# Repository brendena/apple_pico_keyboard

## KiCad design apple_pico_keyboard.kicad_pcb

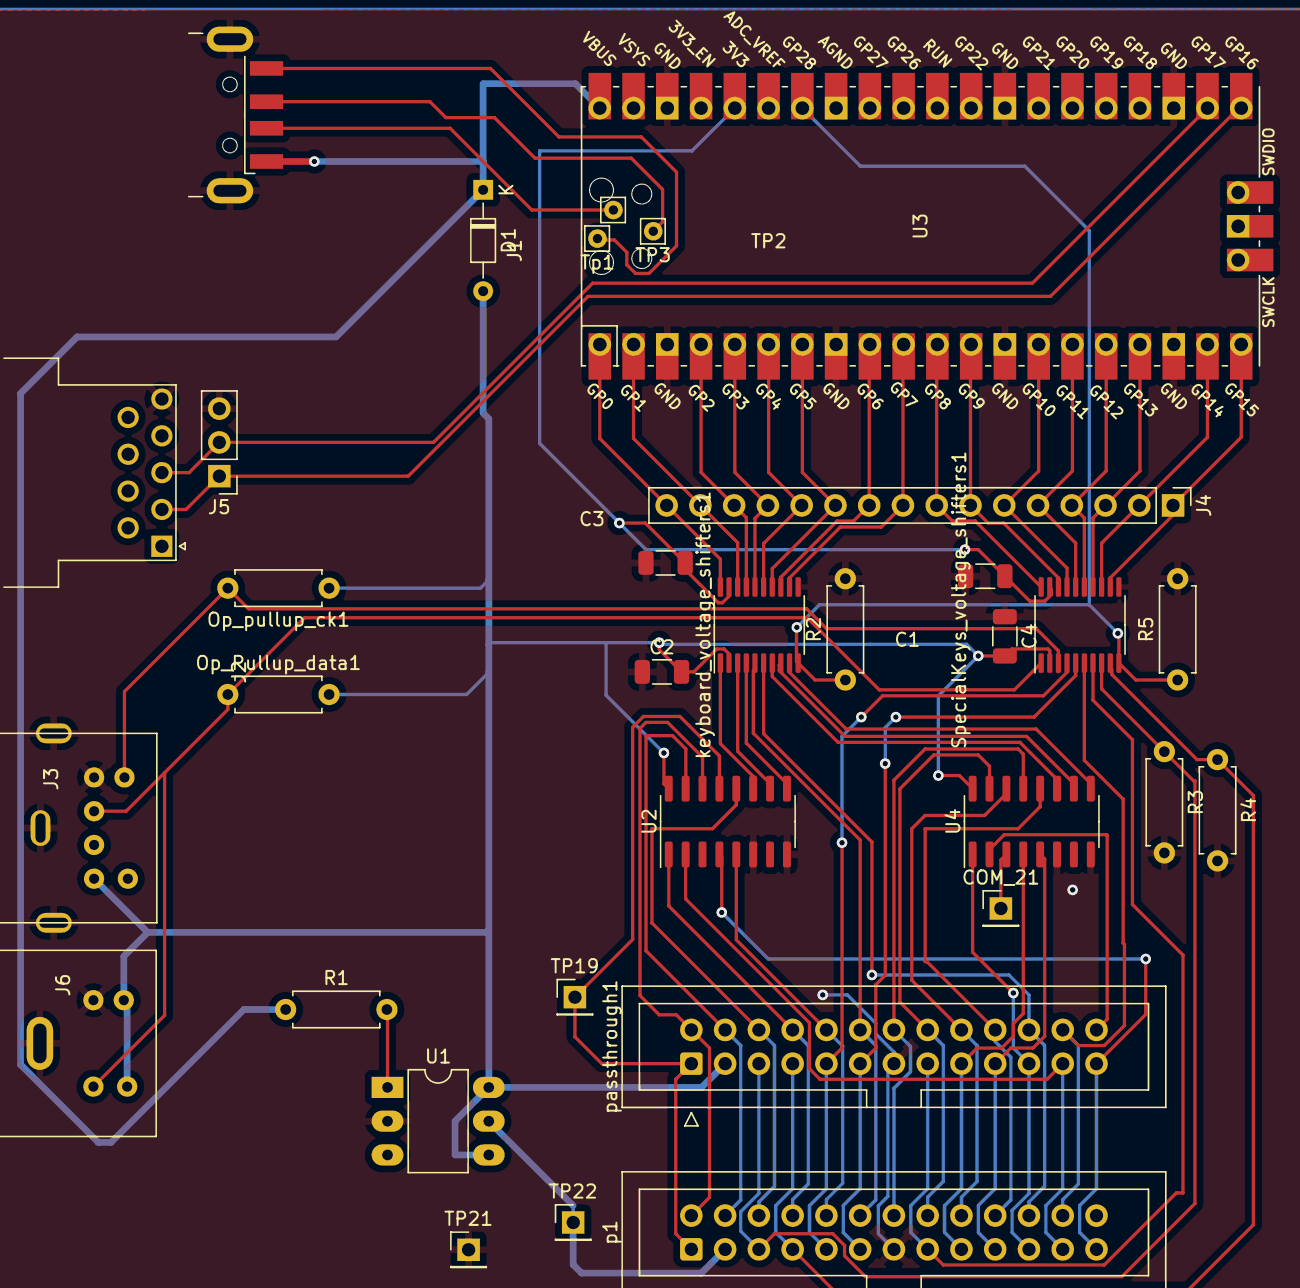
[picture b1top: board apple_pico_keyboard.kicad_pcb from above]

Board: 2 copper layers, 33 parts (0 on the bottom side), 61 nets.

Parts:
C1, C2, C3, C4: 0.1uf; C_1206_3216Metric
COM_21: TestPoint; PinHeader_1x01_P2.54mm_Vertical
D1: DIODE; D_DO-34_SOD68_P7.62mm_Horizontal
J1: USB_A; USB_A_CNCTech_1001-011-01101_Horizontal
J2: DB9_Female; DSUB-9_Female_Horizontal_P2.77x2.54mm_EdgePinOffset9.40mm
J3: Mini-DIN-6; MiniDin6
J4: Conn_01x16_Male; PinHeader_1x16_P2.54mm_Vertical
J5: Conn_01x03_Male; PinHeader_1x03_P2.54mm_Vertical
J6: Mini-DIN-4; MiniDin4
Op_Pullup_data1: 10k; R_Axial_DIN0207_L6.3mm_D2.5mm_P7.62mm_Horizontal
Op_pullup_ck1: 10k; R_Axial_DIN0207_L6.3mm_D2.5mm_P7.62mm_Horizontal
R1: 150; R_Axial_DIN0207_L6.3mm_D2.5mm_P7.62mm_Horizontal
R2, R5: 100?; R_Axial_DIN0207_L6.3mm_D2.5mm_P7.62mm_Horizontal
R3, R4: 470; R_Axial_DIN0207_L6.3mm_D2.5mm_P7.62mm_Horizontal
SpecialKeys_voltage_shifters1: TXS0108EPW; TSSOP-20_4.4x6.5mm_P0.65mm
TP2, TP3: TestPoint; Pin_D0.7mm_L6.5mm_W1.8mm_FlatFork
TP19: TestPoint; PinHeader_1x01_P2.54mm_Vertical
TP21: GndTest; PinHeader_1x01_P2.54mm_Vertical
TP22: 5v_Apple; PinHeader_1x01_P2.54mm_Vertical
Tp1: TestPoint; Pin_D0.7mm_L6.5mm_W1.8mm_FlatFork
U1: TLP592A; DIP-6_W7.62mm_LongPads
U2, U4: SN74HC4851; SOIC-16_3.9x9.9mm_P1.27mm
U3: Pico; RPi_Pico_SMD_TH
keyboard_voltage_shifters1: TXS0108EPW; TSSOP-20_4.4x6.5mm_P0.65mm
p1: apple_2e_keyboard; IDC-Header_2x13_P2.54mm_Vertical
passthrough1: apple_2e_keyboard; IDC-Header_2x13_P2.54mm_Vertical

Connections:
+3V3: C1.2, C3.2, SpecialKeys_voltage_shifters1.19 (VCCB), U3.36 (3V3), keyboard_voltage_shifters1.19 (VCCB)
+5V: C2.2, C4.2, D1.2 (A), J3.4, J6.2, J6.3, Op_Pullup_data1.2, Op_pullup_ck1.1, SpecialKeys_voltage_shifters1.2 (VCCA), U1.4 (D1), U1.6 (D2), U2.16 (VCC), U4.16 (VCC), keyboard_voltage_shifters1.2 (VCCA), passthrough1.3 (5v)
/A_A1: U2.11 (A), keyboard_voltage_shifters1.1 (A1)
/A_A6: U4.11 (A), keyboard_voltage_shifters1.7 (A6)
/B_A2: U2.10 (B), keyboard_voltage_shifters1.3 (A2)
/B_A7: U4.10 (B), keyboard_voltage_shifters1.8 (A7)
/C_A3: U2.9 (C), keyboard_voltage_shifters1.4 (A3)
/C_A8: U4.9 (C), keyboard_voltage_shifters1.9 (A8)
/Cap_pin: SpecialKeys_voltage_shifters1.4 (A3), p1.9 (CAPLOCK), passthrough1.9 (CAPLOCK)
/Ctrl_pin: SpecialKeys_voltage_shifters1.5 (A4), p1.11 (CNTL), passthrough1.11 (CNTL)
/E_LevelShift: R2.1, R5.1, SpecialKeys_voltage_shifters1.10 (OE), U3.34 (GPIO28_ADC2), keyboard_voltage_shifters1.10 (OE)
/PS2_Clock: J3.5, Op_pullup_ck1.2, SpecialKeys_voltage_shifters1.3 (A2)
/PS2_Data: J3.1, J6.1, Op_Pullup_data1.1, SpecialKeys_voltage_shifters1.1 (A1)
/Reset_pin: SpecialKeys_voltage_shifters1.7 (A6), p1.15 (RESET), passthrough1.15 (RESET)
/Shift_pin: SpecialKeys_voltage_shifters1.6 (A5), p1.24 (SHFT*), passthrough1.24 (SHFT*)
/Sw0_pin: R4.1, SpecialKeys_voltage_shifters1.9 (A8), p1.7 (SW0/OAPL), passthrough1.7 (SW0/OAPL)
/Sw1_pin: R3.1, SpecialKeys_voltage_shifters1.8 (A7), p1.5 (SW1/CAPL), passthrough1.5 (SW1/CAPL)
/VBUS: D1.1 (K), J1.1 (VBUS), R1.1, U3.40 (VBUS)
/Y0: TP19.1, U2.13 (Y0), p1.1 (Y0), passthrough1.1 (Y0)
/Y1: U2.14 (Y1), p1.2 (Y1), passthrough1.2 (Y1)
/Y2: U2.15 (Y2), p1.4 (Y2), passthrough1.4 (Y2)
/Y3: U2.12 (Y3), p1.6 (Y3), passthrough1.6 (Y3)
/Y4: U2.1 (Y4), p1.8 (Y4), passthrough1.8 (Y4)
/Y5: U2.5 (Y5), p1.10 (Y5), passthrough1.10 (Y5)
/Y6: U2.2 (Y6), p1.23 (y6), passthrough1.23 (y6)
/Y7: U2.4 (Y7), p1.25 (Y7), passthrough1.25 (Y7)
/Y8: keyboard_voltage_shifters1.5 (A4), p1.12 (y8), passthrough1.12 (y8)
/Y9: keyboard_voltage_shifters1.6 (A5), p1.22 (y9), passthrough1.22 (y9)
/p_g_0: J4.16, U3.1 (GPIO0), keyboard_voltage_shifters1.20 (B1)
/p_g_1: J4.15, U3.2 (GPIO1), keyboard_voltage_shifters1.18 (B2)
/p_g_2: J4.14, U3.4 (GPIO2), keyboard_voltage_shifters1.17 (B3)
/p_g_3: J4.13, U3.5 (GPIO3), keyboard_voltage_shifters1.16 (B4)
/p_g_4: J4.12, U3.6 (GPIO4), keyboard_voltage_shifters1.15 (B5)
/p_g_5: J4.11, U3.7 (GPIO5), keyboard_voltage_shifters1.14 (B6)
/p_g_6: J4.10, U3.9 (GPIO6), keyboard_voltage_shifters1.13 (B7)
/p_g_7: J4.9, U3.10 (GPIO7), keyboard_voltage_shifters1.12 (B8)
/p_g_8: J4.8, SpecialKeys_voltage_shifters1.20 (B1), U3.11 (GPIO8)
/p_g_9: J4.7, SpecialKeys_voltage_shifters1.18 (B2), U3.12 (GPIO9)
/p_g_10: J4.6, SpecialKeys_voltage_shifters1.17 (B3), U3.14 (GPIO10)
/p_g_11: J4.5, SpecialKeys_voltage_shifters1.16 (B4), U3.15 (GPIO11)
/p_g_12: J4.4, SpecialKeys_voltage_shifters1.15 (B5), U3.16 (GPIO12)
/p_g_13: J4.3, SpecialKeys_voltage_shifters1.14 (B6), U3.17 (GPIO13)
/p_g_14: J4.2, SpecialKeys_voltage_shifters1.13 (B7), U3.19 (GPIO14)
/p_g_15: J4.1, SpecialKeys_voltage_shifters1.12 (B8), U3.20 (GPIO15)
/x0: U4.13 (Y0), p1.14 (x0), passthrough1.14 (x0)
/x1: U4.14 (Y1), p1.18 (x1), passthrough1.18 (x1)
/x2: U4.15 (Y2), p1.16 (x2), passthrough1.16 (x2)
/x3: U4.12 (Y3), p1.20 (x3), passthrough1.20 (x3)
/x4: U4.1 (Y4), p1.21 (x4), passthrough1.21 (x4)
/x5: U4.5 (Y5), p1.19 (x5), passthrough1.19 (x5)
/x6: U4.2 (Y6), p1.26 (x6), passthrough1.26 (x6)
/x7: U4.4 (Y7), p1.17 (x7), passthrough1.17 (x7)
GND: C1.1, C2.1, C3.1, C4.1, J1.5 (Shield), J2.5, J3.3, J3.7, J3.8, J3.9, J5.3, J6.4, J6.5, R2.2, R3.2, R4.2, R5.2, SpecialKeys_voltage_shifters1.11 (GND), TP21.1, U1.2 (cathode), U2.6 (INH), U2.8 (GND), U3.3 (GND), U3.8 (GND), U3.13 (GND), U3.18 (GND), U3.23 (GND), U3.28 (GND), U3.38 (GND), U4.6 (INH), U4.8 (GND), keyboard_voltage_shifters1.11 (GND), p1.13 (GND), passthrough1.13 (GND)
unnamed: COM_21.1, U4.3 (Com)
unnamed: J1.2 (D-), TP2.1
unnamed: J1.3 (D+), TP3.1
unnamed: J1.4 (GND), Tp1.1
unnamed: J2.2, J5.1, U3.21 (GPIO16)
unnamed: J2.3, J5.2, U3.22 (GPIO17)
unnamed: R1.2, U1.1 (anode)
unnamed: TP22.1, U1.5 (Source), p1.3 (5v)

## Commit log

2022-10-20 first release
